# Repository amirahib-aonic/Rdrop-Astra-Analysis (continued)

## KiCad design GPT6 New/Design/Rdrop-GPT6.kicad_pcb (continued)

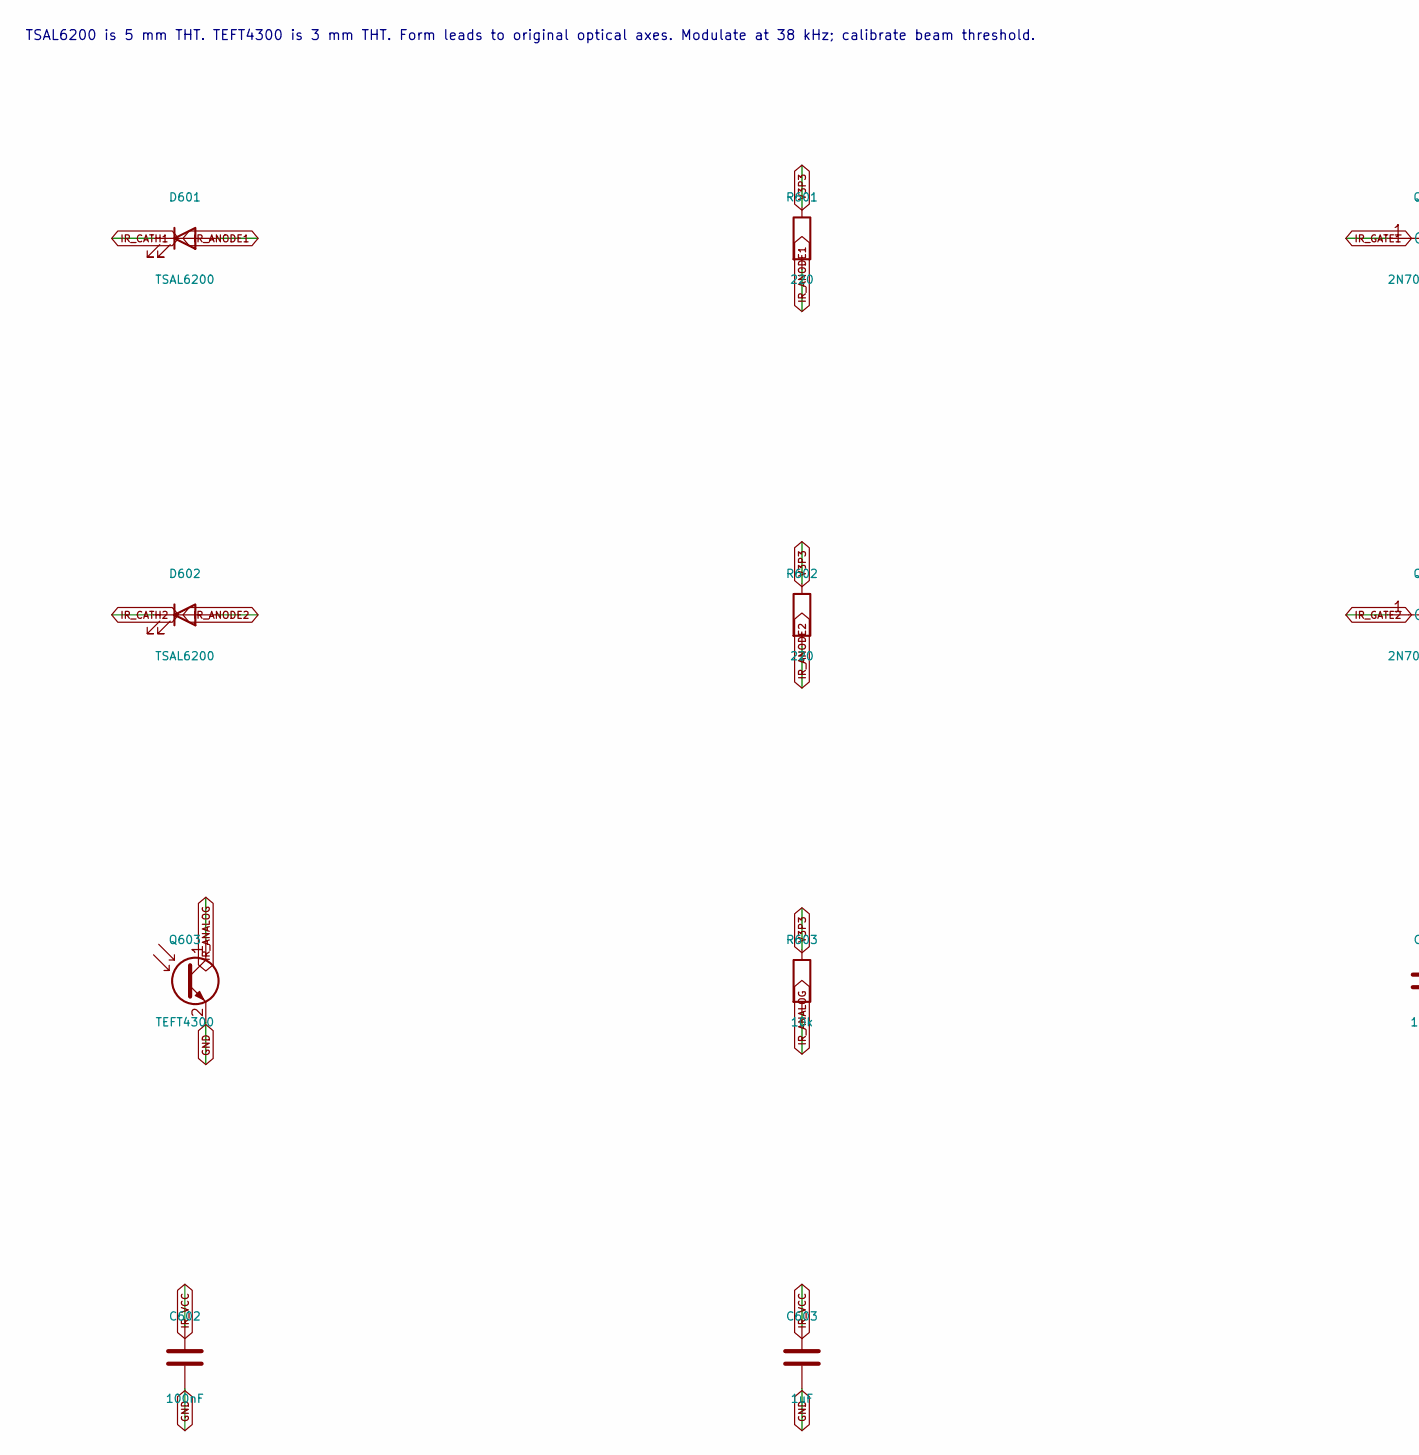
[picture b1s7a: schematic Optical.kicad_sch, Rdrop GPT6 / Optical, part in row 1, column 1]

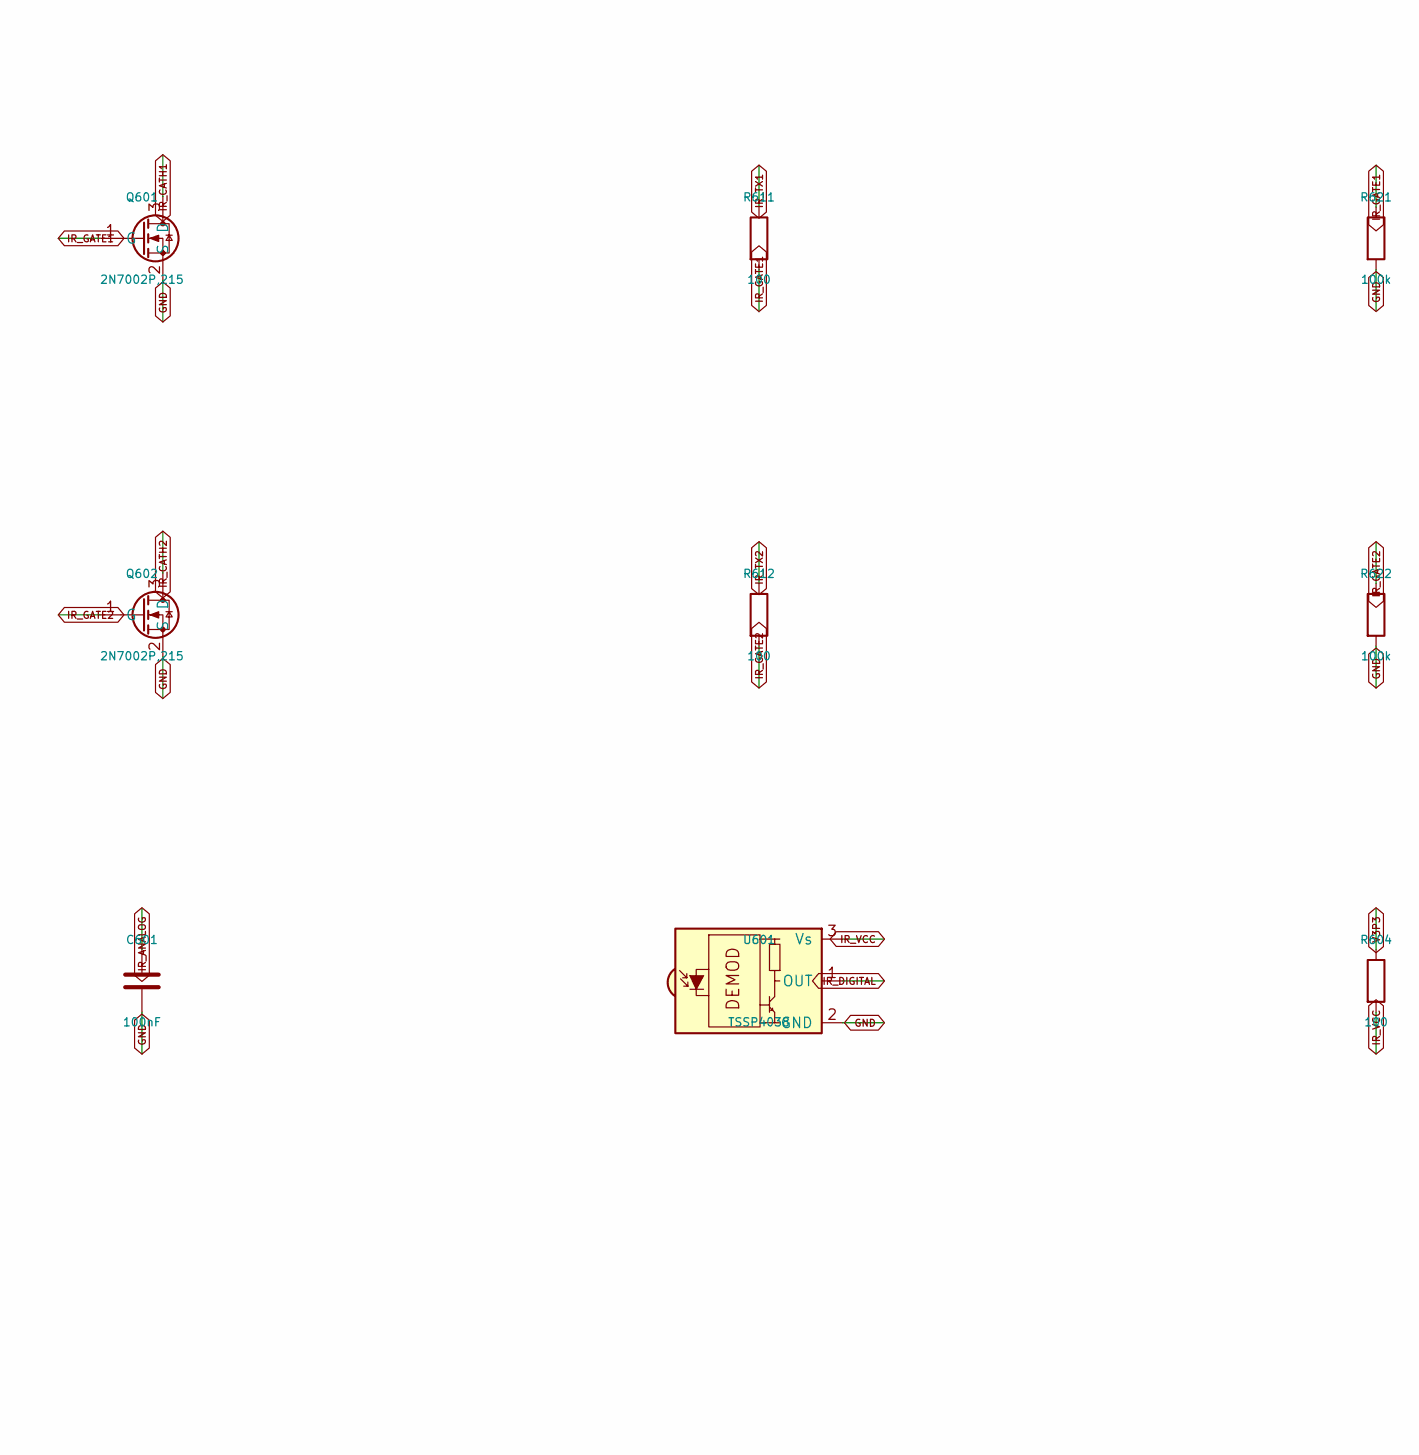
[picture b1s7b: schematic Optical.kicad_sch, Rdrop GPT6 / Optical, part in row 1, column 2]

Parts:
C601, C602: 100nF; C_0603_1608Metric; MPN GRM188R71H104KA93D
C603: 1uF; C_0603_1608Metric; MPN GRM188R61E105KA12D
D601, D602: TSAL6200; LED_D5.0mm_Horizontal_O1.27mm_Z3.0mm; MPN TSAL6200
Q601, Q602: 2N7002P,215; SOT-23; MPN 2N7002P,215
Q603: TEFT4300; LED_D3.0mm_Horizontal_O1.27mm_Z2.0mm; MPN TEFT4300
R601, R602: 220; R_0603_1608Metric; MPN RC0603FR-07220RL
R603: 10k; R_0603_1608Metric; MPN RC0603FR-0710KL
R604, R611, R612: 100; R_0603_1608Metric; MPN RC0603FR-07100RL
R621, R622: 100k; R_0603_1608Metric; MPN RC0603FR-07100KL
U601: TSSP4038; Vishay_MOLD-3Pin; MPN TSSP4038

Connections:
GND: C601.2, C602.2, C603.2, Q601.2 (S), Q602.2 (S), Q603.2 (E), R621.2, R622.2, U601.2 (GND); also elsewhere on the board
IR_ANALOG: C601.1, Q603.1 (C), R603.2; also elsewhere on the board
IR_ANODE1: D601.2 (A), R601.2
IR_ANODE2: D602.2 (A), R602.2
IR_CATH1: D601.1 (K), Q601.3 (D)
IR_CATH2: D602.1 (K), Q602.3 (D)
IR_DIGITAL: U601.1 (OUT); also elsewhere on the board
IR_GATE1: Q601.1 (G), R611.2, R621.1
IR_GATE2: Q602.1 (G), R612.2, R622.1
IR_TX1: R611.1; also elsewhere on the board
IR_TX2: R612.1; also elsewhere on the board
IR_VCC: C602.1, C603.1, R604.2, U601.3 (Vs)
V3P3: R601.1, R602.1, R603.1, R604.1; also elsewhere on the board

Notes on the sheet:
TSAL6200 is 5 mm THT. TEFT4300 is 3 mm THT. Form leads to original optical axes. Modulate at 38 kHz; calibrate beam threshold.

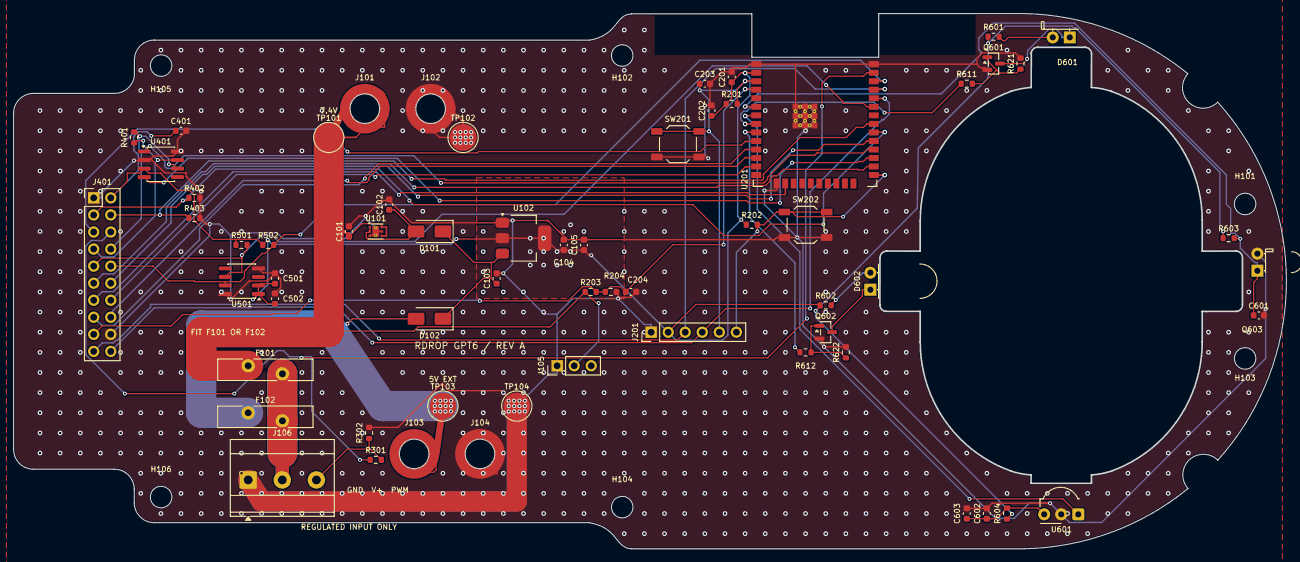
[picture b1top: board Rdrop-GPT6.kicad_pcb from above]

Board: 2 copper layers, 189.5 x 79.7 mm, 69 parts (0 on the bottom side), 40 nets.

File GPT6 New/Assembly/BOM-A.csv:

References,Quantity,Value,MPN,Manufacturer,Footprint
"J101,J102,J103,J104",4,M3 REGULATOR STANDOFF,9774100360R,Wurth Elektronik,Mounting_Wuerth:Mounting_Wuerth_WA-SMSI-M3_H10mm_9774100360
J105,1,UBEC OUT MONITOR,TSW-103-07-G-S,Samtec,Connector_PinHeader_2.54mm:PinHeader_1x03_P2.54mm_Vertical
U101,1,TLV76750DRVR,TLV76750DRVR,Texas Instruments,Package_SON:WSON-6-1EP_2x2mm_P0.65mm_EP1x1.6mm_ThermalVias
"C101,C102,C103,C104,C105,C201",6,10uF,GRM188R61C106KAALD,Murata,Capacitor_SMD:C_0603_1608Metric
"D101,D102",2,SS14,SS14-E3/61T,Vishay,Diode_SMD:D_SMA
U102,1,TLV1117LV33DCYR,TLV1117LV33DCYR,Texas Instruments,Package_TO_SOT_SMD:SOT-223-3_TabPin2
F101,1,MF-RG900-0,MF-RG900-0,Bourns,Fuse:Fuse_Bourns_MF-RG900
J106,1,SERVO GND / V+ / PWM,1711738,Phoenix Contact,TerminalBlock_Phoenix:TerminalBlock_Phoenix_MKDS-3-3-5.08_1x03_P5.08mm_Horizontal
"R301,R611,R612,R604",4,100,RC0603FR-07100RL,Yageo,Resistor_SMD:R_0603_1608Metric
"R302,R203,R402,R403,R621,R622",6,100k,RC0603FR-07100KL,Yageo,Resistor_SMD:R_0603_1608Metric
U201,1,ESP32-WROOM-32E-N4,ESP32-WROOM-32E-N4,Espressif,RF_Module:ESP32-WROOM-32E
"C202,C204,C401,C501,C601,C602",6,100nF,GRM188R71H104KA93D,Murata,Capacitor_SMD:C_0603_1608Metric
"C203,C502,C603",3,1uF,GRM188R61E105KA12D,Murata,Capacitor_SMD:C_0603_1608Metric
"R201,R202,R603",3,10k,RC0603FR-0710KL,Yageo,Resistor_SMD:R_0603_1608Metric
"SW201,SW202",2,RESET,TL3342F160QG,E-Switch,Button_Switch_SMD:SW_SPST_TL3342
J201,1,UART PROGRAM,TSW-106-07-G-S,Samtec,Connector_PinHeader_2.54mm:PinHeader_1x06_P2.54mm_Vertical
R204,1,33k,RC0603FR-0733KL,Yageo,Resistor_SMD:R_0603_1608Metric
J401,1,20-PIN CONTROL,TSW-110-07-G-D,Samtec,Connector_PinHeader_2.54mm:PinHeader_2x10_P2.54mm_Vertical
U401,1,SN65HVD230DR,SN65HVD230DR,Texas Instruments,Package_SO:SOIC-8_3.9x4.9mm_P1.27mm
U501,1,AS5600-ASOM,AS5600-ASOM,ams OSRAM,Package_SO:SOIC-8_3.9x4.9mm_P1.27mm
"R501,R502",2,4.7k,RC0603FR-074K7L,Yageo,Resistor_SMD:R_0603_1608Metric
"D601,D602",2,TSAL6200,TSAL6200,Vishay,LED_THT:LED_D5.0mm_Horizontal_O1.27mm_Z3.0mm
"R601,R602",2,220,RC0603FR-07220RL,Yageo,Resistor_SMD:R_0603_1608Metric
"Q601,Q602",2,"2N7002P,215","2N7002P,215",Nexperia,Package_TO_SOT_SMD:SOT-23
Q603,1,TEFT4300,TEFT4300,Vishay,LED_THT:LED_D3.0mm_Horizontal_O1.27mm_Z2.0mm
U601,1,TSSP4038,TSSP4038,Vishay,OptoDevice:Vishay_MOLD-3Pin
